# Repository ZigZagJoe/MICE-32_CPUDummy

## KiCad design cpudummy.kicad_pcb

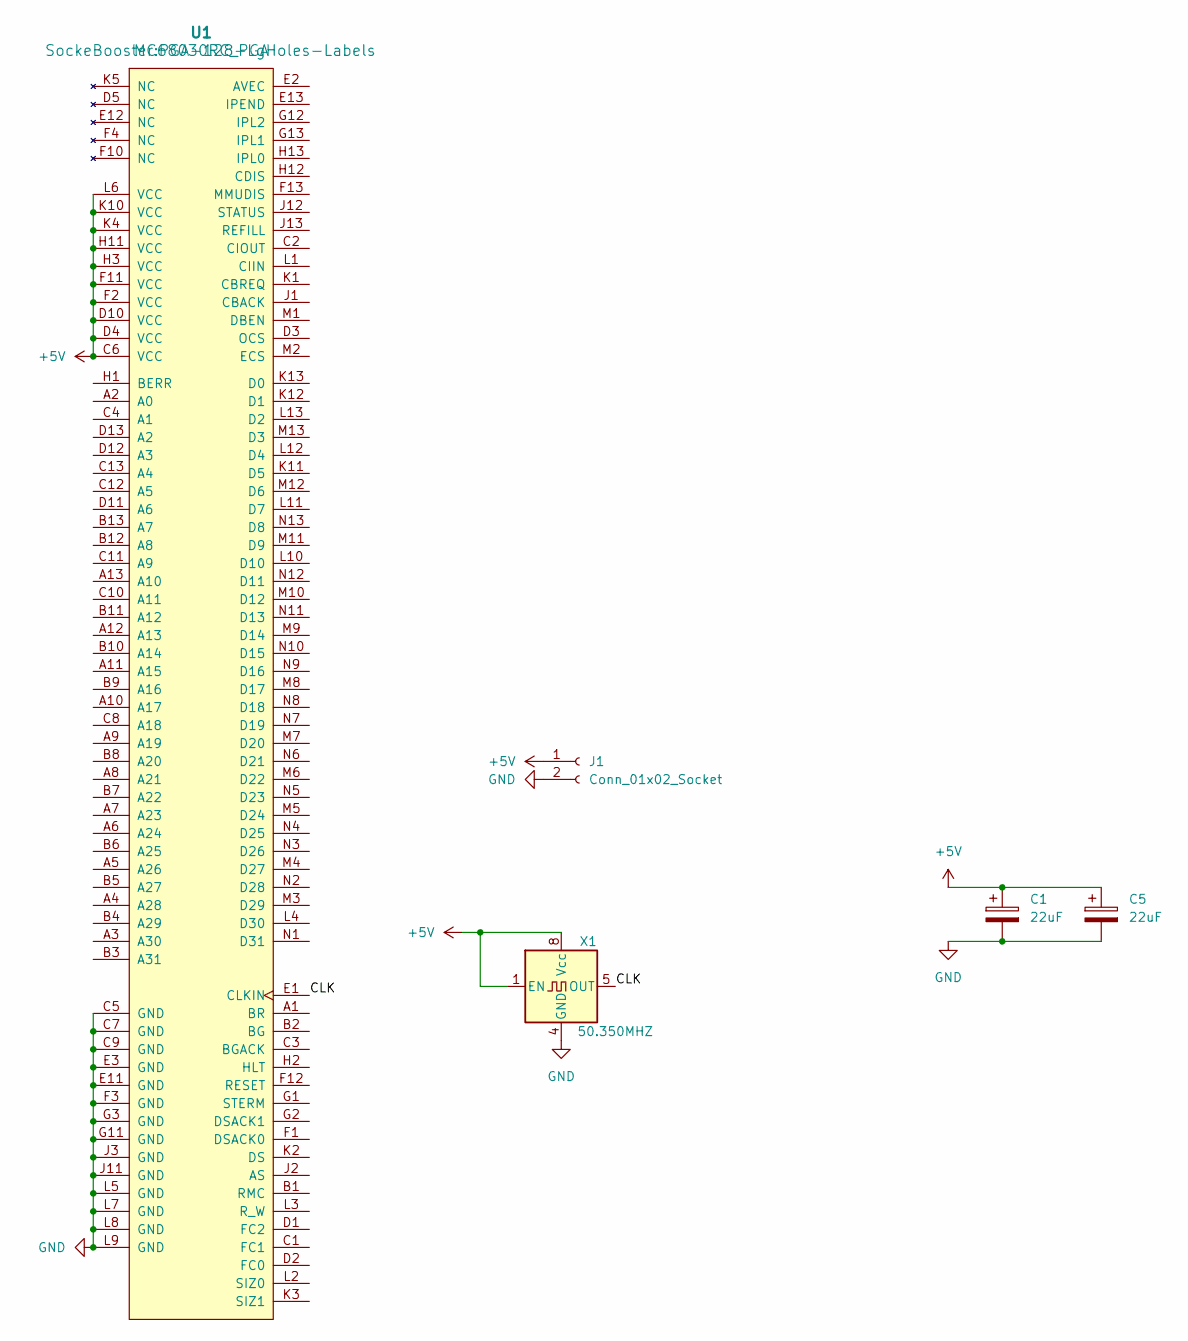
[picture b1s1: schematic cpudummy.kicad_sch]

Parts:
C1, C5: 22uF; C_0805_2012Metric; PartNumber CL21A226MAQNNNE; LCSC C45783
J1: Conn_01x02_Socket; PinHeader_1x02_P2.00mm_Vertical
U1: MC68030RC_PGA; PGA-128-LgHoles-Labels
X1: 50.350MHZ; Oscillator_DIP-8_DIP-14; LCSC n/a

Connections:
+5V: C1.1, C5.1, J1.1, U1.C6 (VCC), U1.D4 (VCC), U1.D10 (VCC), U1.F2 (VCC), U1.F11 (VCC), U1.H3 (VCC), U1.H11 (VCC), U1.K4 (VCC), U1.K10 (VCC), U1.L6 (VCC), X1.1 (EN), X1.8 (Vcc)
/CLK: U1.E1 (CLKIN), X1.5 (OUT)
GND: C1.2, C5.2, J1.2, U1.C5 (GND), U1.C7 (GND), U1.C9 (GND), U1.E3 (GND), U1.E11 (GND), U1.F3 (GND), U1.G3 (GND), U1.G11 (GND), U1.J3 (GND), U1.J11 (GND), U1.L5 (GND), U1.L7 (GND), U1.L8 (GND), U1.L9 (GND), X1.4 (GND)

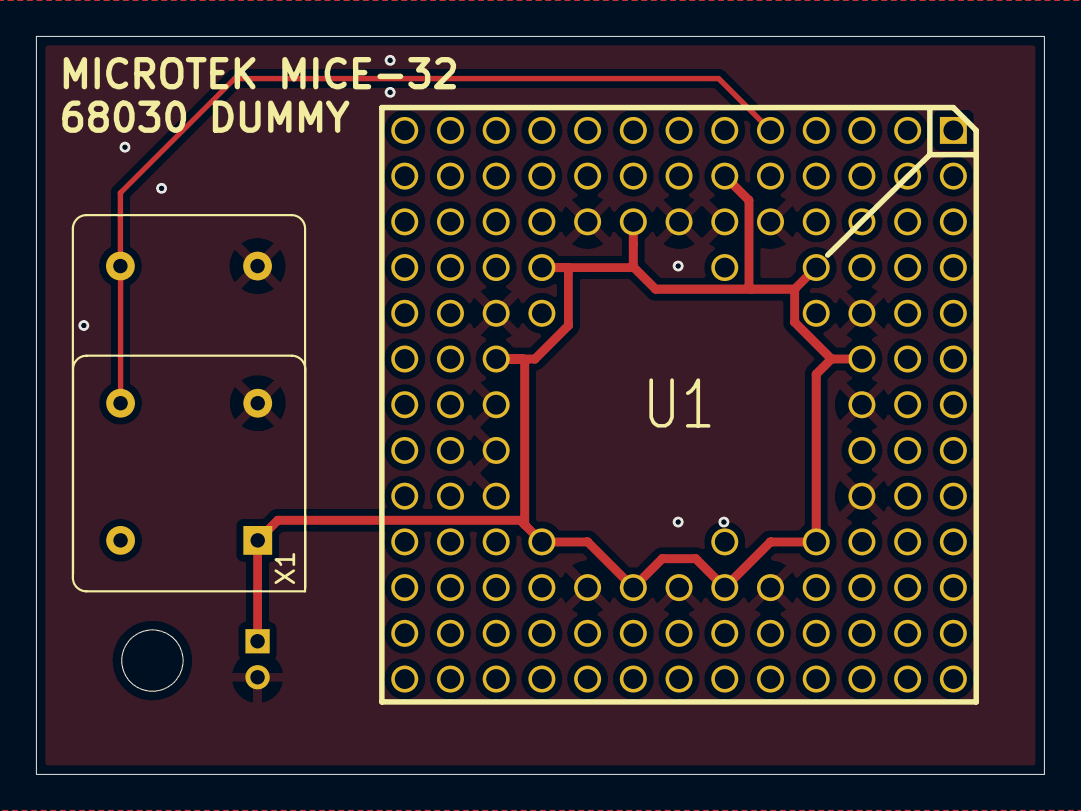
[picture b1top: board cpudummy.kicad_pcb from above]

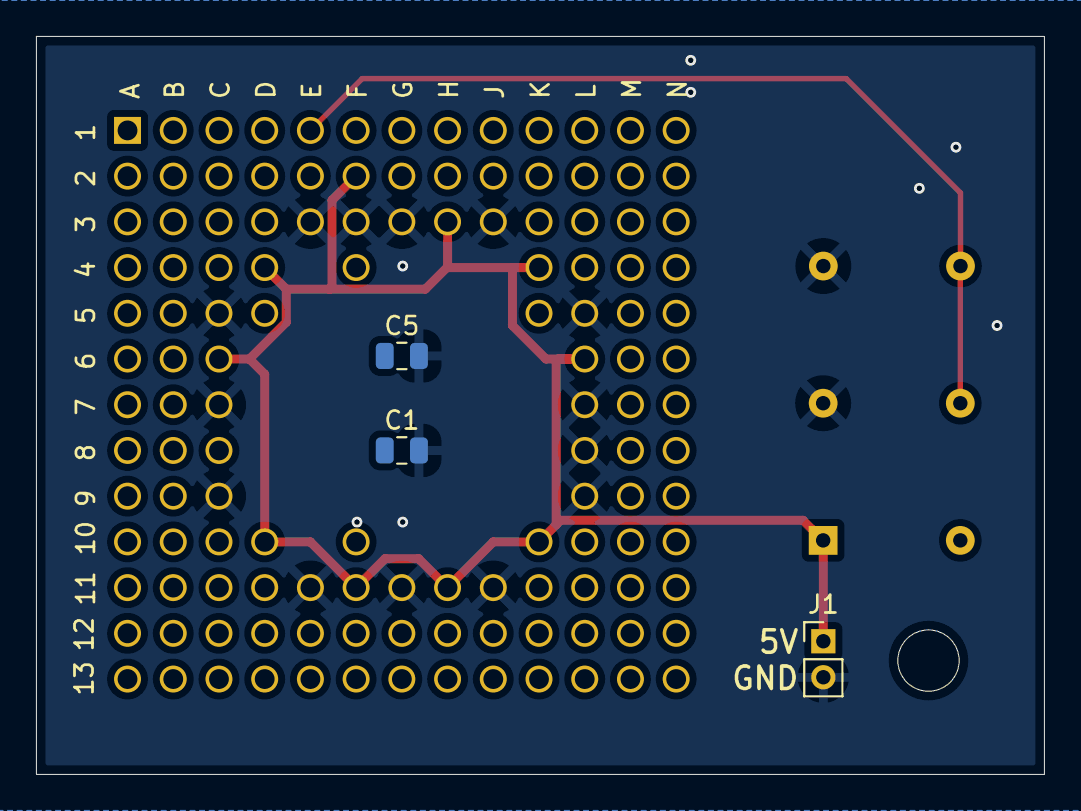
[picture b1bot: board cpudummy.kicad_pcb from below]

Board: 2 copper layers, 56.0 x 41.0 mm, 5 parts (3 on the bottom side), 3 nets.

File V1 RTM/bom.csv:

Designator,Footprint,Quantity,Value,LCSC Part #
"C1, C5",0805,2,22uF,C45783
J1,PinHeader_1x02_P2.00mm_Vertical,1,Conn_01x02_Socket,
U1,PGA-128-LgHoles-Labels,1,MC68030RC_PGA,
X1,Oscillator_DIP-8_DIP-14,1,50.350MHZ,n/a
